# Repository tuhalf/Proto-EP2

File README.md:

# Proto - Educational Pupose 8-Bit Processor
Made for students, teachers, and any soul who wants to understand how a CPU works. Open Source.

Instruction Sets
 I : Instruction 
{ }: Register 
[ ]: Adress
( ): Condition - Based on registers A and B, takes parameters > or =
______________________________________________________________________
ADD [X]
	Add two numbers that are in A and B registers and write it to X address

SUB [X]- Subtract
	Subtract A from B and write it to X address 

LOAD {X} 
	Load data from next adress to X register 

STORE [X]
	Store data form register A to X adress in RAM 

LWJ {X} [Y] - Load With Jump
	Load data from Y adress to X register

JUMP [X]
	Jump to X adress in RAM

CJ (X) [Y] - Conditional Jump (Carry or Zero)
	If X condition is TRUE, jump to Y adress in RAM
  
LSCR [X] [Y]
	Loads the data stored in X address from RAM to Y address from GPU (Each bit is one pixel)
  
LSCR {X} [Y]
	Loads the data stored in X register to Y address from GPU (Each bit is one pixel)
  
LPNC [X]
	Starts loading the punch card starting from X address
  
HLT
	Halts the system

------------------------------------------------------------------------------------------------------------------------------------

Microcode Explained
bits
0nnnn00000nn00__
1000000000000000    HLT - 1
0100000000000000    REG_READ - 2
0010000000000000    AWRITE - 3	(Connected to ALUWRITE and Or'ed with AWRITE because there are not enough controll bits)
0001000000000000    FL - 4
0000100000000000    ALUWRITE - 5(Connected to RAM_WRITE and Or'ed with AWRITE because there are not enough controll bits)
0000010000000000    ALUSUB - 6
0000001000000000    PC_LE - 7
0000000100000000    PC_LRS - 8
0000000010000000    RAM_LRS - 9
0000000001000000    SLC_ADDR - 10
0000000000100000    RAM_OUT - 11
0000000000010000    INSTREAD - 12
0000000000001000    COUNT - 13
0000000000000100    RAM_AS - 14
0000000000000010    --
0000000000000001    --
01111000 00110000				00------000
----JUMP [X]---- (N-------,XXXXXXXX,XXXXXXXX)	nn100000                        
COUNT						00100000000 - 01111000 00111000
PC_LRS || RAM_OUT				00100000100 - 01111001 00010000
COUNT						00100000010 - 01111000 00111000	
RAM_OUT || PC_LE			        00100000110 - 01111010 00010000
RAM_OUT || INSTREAD				00100000001 - 01111000 00000000
----------------
----LOAD {X}---- (X-------)			                nn010000    
COUNT                                           00010000000 - 01111000 00111000
RAM_OUT || REG_READ                             00010000100 - 00111000 00010000
COUNT                                           00010000010 - 01111000 00111000
RAM_OUT || INSTREAD                             00010000110 - 01111000 00000000
----------------
----ADD [X]---- (N-------,XXXXXXXX,XXXXXXXX)    nn110000
COUNT || RAM_OUT || RAM_LRS || SLC_ADDR         00110000000 - 01111000 11011000
COUNT || RAM_OUT || SLC_ADDR                    00110000100 - 01111000 01011000
RAM_AS || ALUWRITE                              00110000010 - 01110000 00110100
RAM_OUT || INSTREAD                             00110000110 - 01111000 00000000
----------------
----SUB [X]---- (N-------,XXXXXXXX,XXXXXXXX)    nn001000
COUNT || RAM_OUT || RAM_LRS || SLC_ADDR         00001000000 - 01111000 11011000
COUNT || RAM_OUT || SLC_ADDR                    00001000100 - 01111000 01011000
RAM_AS || ALUSUB || ALUWRITE                    00001000010 - 01110100 00110100
RAM_OUT || INSTREAD                             00001000110 - 01111000 00000000
----------------
----STORE [X]---- (N-------,XXXXXXXX,XXXXXXXX)  nn101000
COUNT || RAM_OUT || RAM_LRS || SLC_ADDR         00101000000 - 01111000 11011000
COUNT || RAM_OUT || SLC_ADDR                    00101000100 - 01111000 01011000
RAM_AS || AWRITE                                00101000010 - 01011000 00110100
RAM_OUT || INSTREAD                             00101000110 - 01111000 00000000
-----------------
----LWJ {X} [Y]---- (X-------,YYYYYYYY,YYYYYYYY)nn111000
COUNT || RAM_OUT || RAM_LRS || SLC_ADDR         00111000000 - 01111000 11011000
COUNT || RAM_OUT || SLC_ADDR                    00111000100 - 01111000 01011000
RAM_AS || RAM_OUT || REG_READ                   00111000010 - 00111000 00010100
RAM_OUT || INSTREAD                             00111000110 - 01111000 00000000
-------------------
----CJ (ZERO) [Y]-- (N-1-----,XXXXXXXX,XXXXXXXX)nn001100
COUNT || FL                                     00001100000 - 01101000 00111000
01OOOOOO[PC_LRS || RAM_OUT                      01001100100 - 01111001 00010000
COUNT || RAM_OUT || PC_LE                       01001100010 - 01111010 00011000
RAM_OUT || INSTREAD]                            01001100110 - 01111000 00000000
COUNT                                           00001100100 - 01111000 00111000
COUNT || RAM_OUT || INSTREAD                    00001100010 - 01111000 00001000
---------------------
---CJ (CARRY) [Y]-- (N-1-----,XXXXXXXX,XXXXXXXX)nn100100
COUNT || FL                                     00100100000 - 01101000 00111000
10OOOOOO[PC_LRS || RAM_OUT                      10100100100 - 01111001 00010000
COUNT || RAM_OUT || PC_LE                       10100100010 - 01111010 00011000
RAM_OUT || INSTREAD]                            10100100110 - 01111000 00000000
COUNT                                           00100100100 - 01111000 00111000
COUNT || RAM_OUT || INSTREAD                    00100100010 - 01111000 00001000
---------------------
----HLT----                                     nn111111
HLT                                             00111111000 - 11111000 00110000
-----------

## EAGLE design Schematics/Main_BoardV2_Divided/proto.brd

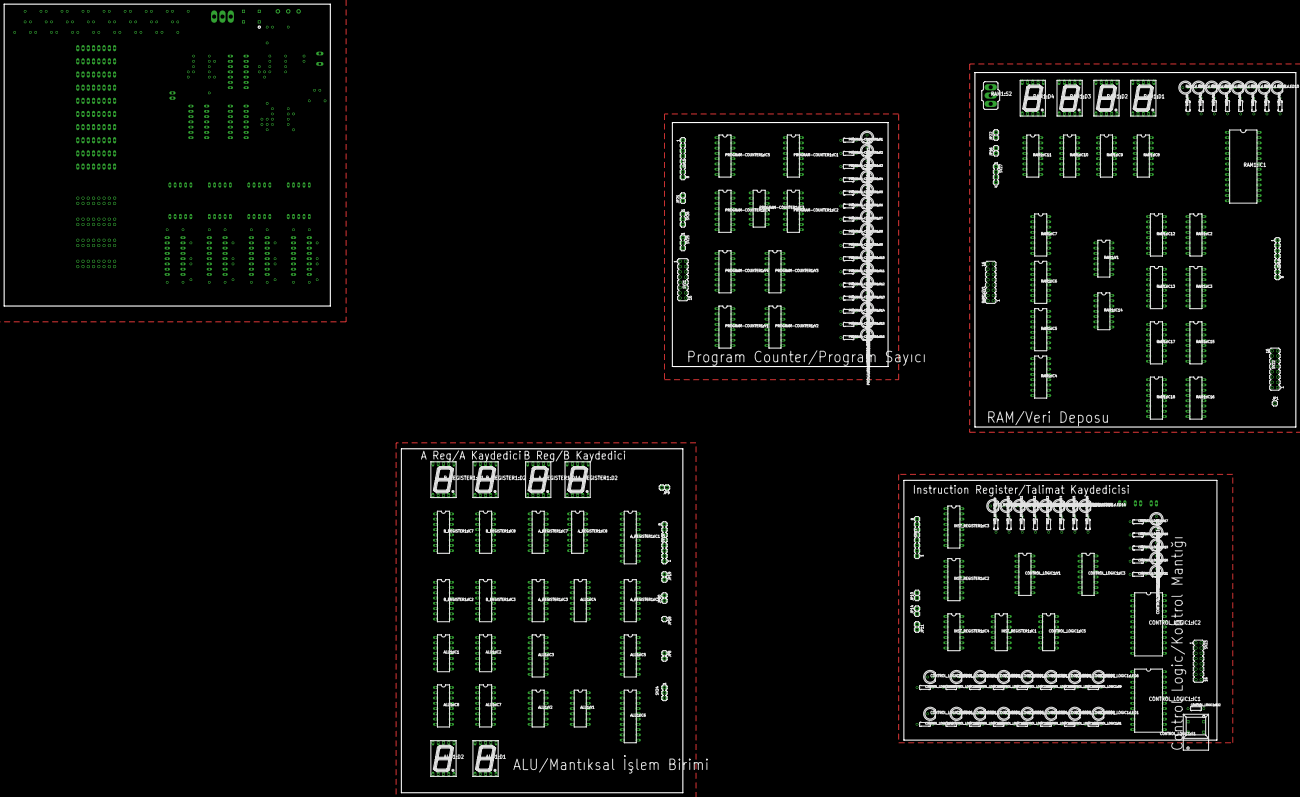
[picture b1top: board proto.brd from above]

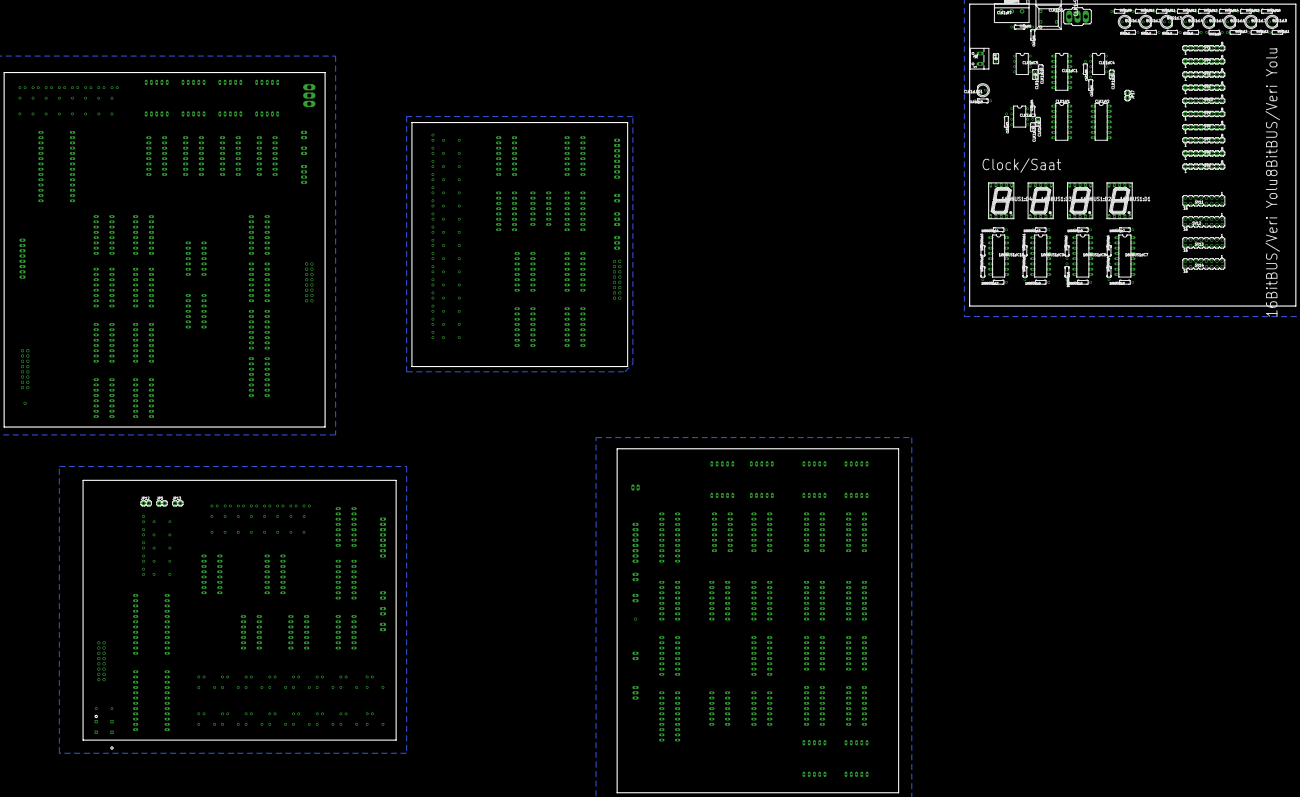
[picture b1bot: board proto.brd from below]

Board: 2 copper layers, 623.5 x 380.7 mm, 289 parts (90 on the bottom side), 422 nets, no tracks yet.

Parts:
16BBUS1:1, 16BBUS1:2, 16BBUS1:3, 16BBUS1:4, 16BBUS1:5, 16BBUS1:6, 16BBUS1:7, 16BBUS1:8, 16BBUS1:9, 16BBUS1:10, 16BBUS1:11, 16BBUS1:12, 16BBUS1:13, 16BBUS1:14, 16BBUS1:15, 16BBUS1:16: 10k; 0204/7
16BBUS1:D1, 16BBUS1:D2, 16BBUS1:D3, 16BBUS1:D4: 7SEG-13
16BBUS1:IC7, 16BBUS1:IC8, 16BBUS1:IC9, 16BBUS1:IC10: 74LS47N; DIL16
ALU1:D1, ALU1:D2: 7SEG-13
ALU1:IC1, ALU1:IC2: 74LS86N; DIL14
ALU1:IC3, ALU1:IC4: 74AC283N; DIL16
ALU1:IC5: 74HC173N; DIL16
ALU1:IC6: 74ACT245N; DIL20
ALU1:IC7, ALU1:IC8: 74LS47N; DIL16
ALU1:V1: 744002N; DIL14
ALU1:V2: 7409N; DIL14
A_REGISTER1:D1, A_REGISTER1:D2: 7SEG-13
A_REGISTER1:IC1: 74ACT245N; DIL20
A_REGISTER1:IC2, A_REGISTER1:IC3: 74HC173N; DIL16
A_REGISTER1:IC7, A_REGISTER1:IC8: 74LS47N; DIL16
BUS1:1, BUS1:2, BUS1:3, BUS1:5, BUS1:11, BUS1:12, BUS1:13, BUS1:15: 10k; 0204/7
BUS1:L1, BUS1:L2, BUS1:L3, BUS1:L4, BUS1:L5, BUS1:L6, BUS1:L7, BUS1:L8: LED5MM
BUS1:R9, BUS1:R10, BUS1:R11, BUS1:R12, BUS1:R13, BUS1:R14, BUS1:R15, BUS1:R16: 220; 0204/7
B_REGISTER1:D1, B_REGISTER1:D2: 7SEG-13
B_REGISTER1:IC2, B_REGISTER1:IC3: 74HC173N; DIL16
B_REGISTER1:IC7, B_REGISTER1:IC8: 74LS47N; DIL16
C1: 330uf; C025-025X050
CLK1:C1: 1uf; C025-024X044
CLK1:C2: 0.01uF; C025-025X050
CLK1:C3, CLK1:C5: 0.01uF; C025-024X044
CLK1:C4: 0.1uf; C025-024X044
CLK1:IC1: 74ALS09N; DIL14
CLK1:IC3, CLK1:IC4, CLK1:IC5: LM555N; DIL08
CLK1:LED1: LED5MM
CLK1:R1, CLK1:R2, CLK1:R3, CLK1:R4, CLK1:R5, CLK1:R6: 1k; 0204/7
CLK1:R7: 3RP/1610N
CLK1:R13: 220; 0204/7
CLK1:S1: 5501
CLK1:S2: 320-916
CLK1:V1: 7404N; DIL14
CLK1:V2: 7432N; DIL14
CONTROL_LOGIC1:IC1, CONTROL_LOGIC1:IC2: DIL24
CONTROL_LOGIC1:IC3: 74AC138N; DIL16
CONTROL_LOGIC1:IC5: 74AC00N; DIL14
CONTROL_LOGIC1:LED1, CONTROL_LOGIC1:LED2, CONTROL_LOGIC1:LED3, CONTROL_LOGIC1:LED4, CONTROL_LOGIC1:LED5, CONTROL_LOGIC1:LED6, CONTROL_LOGIC1:LED7, CONTROL_LOGIC1:LED8, CONTROL_LOGIC1:LED9, CONTROL_LOGIC1:LED10, CONTROL_LOGIC1:LED11, CONTROL_LOGIC1:LED12, CONTROL_LOGIC1:LED13, CONTROL_LOGIC1:LED14, CONTROL_LOGIC1:LED15, CONTROL_LOGIC1:LED16, CONTROL_LOGIC1:LED17, CONTROL_LOGIC1:LED18, CONTROL_LOGIC1:LED19, CONTROL_LOGIC1:LED20, CONTROL_LOGIC1:LED21: LED5MM
CONTROL_LOGIC1:R1, CONTROL_LOGIC1:R2, CONTROL_LOGIC1:R3, CONTROL_LOGIC1:R4, CONTROL_LOGIC1:R5, CONTROL_LOGIC1:R6, CONTROL_LOGIC1:R7, CONTROL_LOGIC1:R8, CONTROL_LOGIC1:R9, CONTROL_LOGIC1:R10, CONTROL_LOGIC1:R11, CONTROL_LOGIC1:R12, CONTROL_LOGIC1:R13, CONTROL_LOGIC1:R14, CONTROL_LOGIC1:R15, CONTROL_LOGIC1:R16, CONTROL_LOGIC1:R17, CONTROL_LOGIC1:R18, CONTROL_LOGIC1:R19, CONTROL_LOGIC1:R20, CONTROL_LOGIC1:R21, CONTROL_LOGIC1:R22: 220; 0204/7
CONTROL_LOGIC1:S1: 5501
CONTROL_LOGIC1:V1: 74161N; DIL16
INST_REGISTER1:IC1: 74ALS09N; DIL14
INST_REGISTER1:IC2, INST_REGISTER1:IC3: 74HC173N; DIL16
INST_REGISTER1:IC4: 74AC04N; DIL14
INST_REGISTER1:LED9, INST_REGISTER1:LED10, INST_REGISTER1:LED11, INST_REGISTER1:LED12, INST_REGISTER1:LED13, INST_REGISTER1:LED14, INST_REGISTER1:LED15, INST_REGISTER1:LED16: LED5MM
INST_REGISTER1:R9, INST_REGISTER1:R10, INST_REGISTER1:R11, INST_REGISTER1:R12, INST_REGISTER1:R13, INST_REGISTER1:R14, INST_REGISTER1:R15, INST_REGISTER1:R16: 220; 0204/7
JP1, JP18: 1X01
JP5, JP8, JP9, JP10, JP11, JP12, JP13, JP14, JP16, JP17, JP19, JP20, JP21, JP22: 1X02
PROGRAM-COUNTER1:IC1, PROGRAM-COUNTER1:IC2, PROGRAM-COUNTER1:IC4, PROGRAM-COUNTER1:IC5: 74HC173N; DIL16
PROGRAM-COUNTER1:IC3: 74AC04N; DIL14
PROGRAM-COUNTER1:LED1, PROGRAM-COUNTER1:LED2, PROGRAM-COUNTER1:LED3, PROGRAM-COUNTER1:LED4, PROGRAM-COUNTER1:LED5, PROGRAM-COUNTER1:LED6, PROGRAM-COUNTER1:LED7, PROGRAM-COUNTER1:LED8, PROGRAM-COUNTER1:LED9, PROGRAM-COUNTER1:LED10, PROGRAM-COUNTER1:LED11, PROGRAM-COUNTER1:LED12, PROGRAM-COUNTER1:LED13, PROGRAM-COUNTER1:LED14, PROGRAM-COUNTER1:LED15, PROGRAM-COUNTER1:LED16: LED5MM
PROGRAM-COUNTER1:R1, PROGRAM-COUNTER1:R2, PROGRAM-COUNTER1:R3, PROGRAM-COUNTER1:R4, PROGRAM-COUNTER1:R5, PROGRAM-COUNTER1:R6, PROGRAM-COUNTER1:R7, PROGRAM-COUNTER1:R8, PROGRAM-COUNTER1:R9, PROGRAM-COUNTER1:R10, PROGRAM-COUNTER1:R11, PROGRAM-COUNTER1:R12, PROGRAM-COUNTER1:R13, PROGRAM-COUNTER1:R14, PROGRAM-COUNTER1:R15, PROGRAM-COUNTER1:R16: 220; 0204/7
PROGRAM-COUNTER1:V1, PROGRAM-COUNTER1:V2, PROGRAM-COUNTER1:V3, PROGRAM-COUNTER1:V4: 74161N; DIL16
RAM1:D1, RAM1:D2, RAM1:D3, RAM1:D4: 7SEG-13
RAM1:IC1: CY62256LL-PC; DIL28-6
RAM1:IC2, RAM1:IC3, RAM1:IC12, RAM1:IC13: 74HC173N; DIL16
RAM1:IC4, RAM1:IC5, RAM1:IC6, RAM1:IC7, RAM1:IC15, RAM1:IC16, RAM1:IC17, RAM1:IC18: 74AC157N; DIL16
RAM1:IC8, RAM1:IC9, RAM1:IC10, RAM1:IC11: 74LS47N; DIL16
RAM1:IC14: 74AC04N; DIL14
RAM1:LED9, RAM1:LED10, RAM1:LED11, RAM1:LED12, RAM1:LED13, RAM1:LED14, RAM1:LED15, RAM1:LED16: LED5MM
RAM1:R9, RAM1:R10, RAM1:R11, RAM1:R12, RAM1:R13, RAM1:R14, RAM1:R15, RAM1:R16: 220; 0204/7
RAM1:S2: 320-916
RAM1:SV1: MA08-2
RAM1:V1: 7409N; DIL14
SV1, SV2, SV3, SV4, SV5, SV6, SV7, SV8, SV9, SV10, SV15, SV16, SV17, SV18: MA08-1
SV11, SV12, SV13, SV14, SV21, SV22, SV23: MA08-2
SV24, SV25, SV26: MA03-1
SV27: MA04-1
X1: W237-102

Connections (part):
8B_1: ALU1:IC6.18, A_REGISTER1:IC1.18, A_REGISTER1:IC3.14, B_REGISTER1:IC3.14, INST_REGISTER1:IC3.14, PROGRAM-COUNTER1:IC1.14, PROGRAM-COUNTER1:IC5.14, RAM1:IC1.11, RAM1:IC2.14, RAM1:IC12.14, RAM1:LED9.A, SV15.1, SV16.1, SV17.8, SV18.8
8B_2: ALU1:IC6.17, A_REGISTER1:IC1.17, A_REGISTER1:IC3.13, B_REGISTER1:IC3.13, INST_REGISTER1:IC3.13, PROGRAM-COUNTER1:IC1.13, PROGRAM-COUNTER1:IC5.13, RAM1:IC1.12, RAM1:IC2.13, RAM1:IC12.13, RAM1:LED10.A, SV15.2, SV16.2, SV17.7, SV18.7
8B_3: ALU1:IC6.16, A_REGISTER1:IC1.16, A_REGISTER1:IC3.12, B_REGISTER1:IC3.12, INST_REGISTER1:IC3.12, PROGRAM-COUNTER1:IC1.12, PROGRAM-COUNTER1:IC5.12, RAM1:IC1.13, RAM1:IC2.12, RAM1:IC12.12, RAM1:LED11.A, SV15.3, SV16.3, SV17.6, SV18.6
8B_4: ALU1:IC6.15, A_REGISTER1:IC1.15, A_REGISTER1:IC3.11, B_REGISTER1:IC3.11, INST_REGISTER1:IC3.11, PROGRAM-COUNTER1:IC1.11, PROGRAM-COUNTER1:IC5.11, RAM1:IC1.15, RAM1:IC2.11, RAM1:IC12.11, RAM1:LED12.A, SV15.4, SV16.4, SV17.5, SV18.5
8B_5: ALU1:IC6.14, A_REGISTER1:IC1.14, A_REGISTER1:IC2.14, INST_REGISTER1:IC2.14, PROGRAM-COUNTER1:IC2.14, PROGRAM-COUNTER1:IC4.14, RAM1:IC1.16, RAM1:IC3.14, RAM1:IC13.14, RAM1:LED13.A, SV15.5, SV16.5, SV17.4, SV18.4
8B_6: ALU1:IC6.13, A_REGISTER1:IC1.13, A_REGISTER1:IC2.13, INST_REGISTER1:IC2.13, PROGRAM-COUNTER1:IC2.13, PROGRAM-COUNTER1:IC4.13, RAM1:IC1.17, RAM1:IC3.13, RAM1:IC13.13, RAM1:LED14.A, SV15.6, SV16.6, SV17.3, SV18.3
8B_7: ALU1:IC6.12, A_REGISTER1:IC1.12, A_REGISTER1:IC2.12, INST_REGISTER1:IC2.12, PROGRAM-COUNTER1:IC2.12, PROGRAM-COUNTER1:IC4.12, RAM1:IC1.18, RAM1:IC3.12, RAM1:IC13.12, RAM1:LED15.A, SV15.7, SV16.7, SV17.2, SV18.2
8B_8: ALU1:IC6.11, A_REGISTER1:IC1.11, A_REGISTER1:IC2.11, INST_REGISTER1:IC2.11, PROGRAM-COUNTER1:IC2.11, PROGRAM-COUNTER1:IC4.11, RAM1:IC1.19, RAM1:IC3.11, RAM1:IC13.11, RAM1:LED16.A, SV15.8, SV16.8, SV17.1, SV18.1
16BBUS1:N$9: 16BBUS1:D1.7, 16BBUS1:IC7.13
16BBUS1:N$10: 16BBUS1:D1.6, 16BBUS1:IC7.12
16BBUS1:N$11: 16BBUS1:D1.4, 16BBUS1:IC7.11
16BBUS1:N$12: 16BBUS1:D1.2, 16BBUS1:IC7.10
16BBUS1:N$13: 16BBUS1:D1.1, 16BBUS1:IC7.9
16BBUS1:N$14: 16BBUS1:D1.9, 16BBUS1:IC7.15
16BBUS1:N$15: 16BBUS1:D1.10, 16BBUS1:IC7.14
16BBUS1:N$16: 16BBUS1:D2.7, 16BBUS1:IC8.13
16BBUS1:N$17: 16BBUS1:D4.7, 16BBUS1:IC10.13
16BBUS1:N$18: 16BBUS1:D4.6, 16BBUS1:IC10.12
16BBUS1:N$19: 16BBUS1:D4.4, 16BBUS1:IC10.11
16BBUS1:N$20: 16BBUS1:D4.2, 16BBUS1:IC10.10
16BBUS1:N$21: 16BBUS1:D2.6, 16BBUS1:IC8.12
16BBUS1:N$22: 16BBUS1:D2.4, 16BBUS1:IC8.11
16BBUS1:N$23: 16BBUS1:D2.2, 16BBUS1:IC8.10
16BBUS1:N$24: 16BBUS1:D2.1, 16BBUS1:IC8.9
16BBUS1:N$25: 16BBUS1:D4.1, 16BBUS1:IC10.9
16BBUS1:N$26: 16BBUS1:D4.9, 16BBUS1:IC10.15
16BBUS1:N$27: 16BBUS1:D4.10, 16BBUS1:IC10.14
16BBUS1:N$29: 16BBUS1:D2.9, 16BBUS1:IC8.15
16BBUS1:N$30: 16BBUS1:D2.10, 16BBUS1:IC8.14
16BBUS1:N$31: 16BBUS1:D3.7, 16BBUS1:IC9.13
16BBUS1:N$32: 16BBUS1:D3.6, 16BBUS1:IC9.12
16BBUS1:N$33: 16BBUS1:D3.4, 16BBUS1:IC9.11
16BBUS1:N$34: 16BBUS1:D3.2, 16BBUS1:IC9.10
16BBUS1:N$35: 16BBUS1:D3.1, 16BBUS1:IC9.9
16BBUS1:N$36: 16BBUS1:D3.9, 16BBUS1:IC9.15
16BBUS1:N$37: 16BBUS1:D3.10, 16BBUS1:IC9.14
16BBUS1:VCC: 16BBUS1:D1.3, 16BBUS1:D1.5, 16BBUS1:D1.8, 16BBUS1:D2.3, 16BBUS1:D2.5, 16BBUS1:D2.8, 16BBUS1:D3.3, 16BBUS1:D3.5, 16BBUS1:D3.8, 16BBUS1:D4.3, 16BBUS1:D4.5, 16BBUS1:D4.8, 16BBUS1:IC7.16, 16BBUS1:IC8.16, 16BBUS1:IC9.16, 16BBUS1:IC10.16
ALU1:+UB: ALU1:V1.14, ALU1:V2.14
ALU1:-UB: ALU1:V1.7, ALU1:V2.7
ALU1:A_9: ALU1:IC4.4, ALU1:IC6.9, ALU1:IC8.7, ALU1:V1.9
ALU1:A_10: ALU1:IC4.1, ALU1:IC6.8, ALU1:IC8.1, ALU1:V1.10
ALU1:A_11: ALU1:IC4.10, ALU1:IC6.6, ALU1:IC8.6, ALU1:V1.12
ALU1:A_12: ALU1:IC4.13, ALU1:IC6.7, ALU1:IC8.2, ALU1:V1.11
ALU1:A_13: ALU1:IC3.4, ALU1:IC6.5, ALU1:IC7.7, ALU1:V1.2
ALU1:A_14: ALU1:IC3.1, ALU1:IC6.4, ALU1:IC7.1, ALU1:V1.3
ALU1:A_15: ALU1:IC3.13, ALU1:IC6.3, ALU1:IC7.2, ALU1:V1.4
ALU1:A_16: ALU1:IC3.10, ALU1:IC6.2, ALU1:IC7.6, ALU1:V1.5
ALU1:N$1: ALU1:IC2.11, ALU1:IC4.6
ALU1:N$2: ALU1:IC2.8, ALU1:IC4.2
ALU1:N$3: ALU1:IC2.6, ALU1:IC4.15
ALU1:N$4: ALU1:IC2.3, ALU1:IC4.11
ALU1:N$5: ALU1:IC1.11, ALU1:IC3.6
ALU1:N$6: ALU1:IC1.6, ALU1:IC3.15
ALU1:N$7: ALU1:IC1.8, ALU1:IC3.2
ALU1:N$8: ALU1:IC1.3, ALU1:IC3.11
ALU1:N$9: ALU1:IC3.7, ALU1:IC4.9
ALU1:N$10: ALU1:D1.7, ALU1:IC7.13
ALU1:N$11: ALU1:D1.6, ALU1:IC7.12
ALU1:N$12: ALU1:D1.4, ALU1:IC7.11
ALU1:N$13: ALU1:D1.2, ALU1:IC7.10
ALU1:N$14: ALU1:D1.1, ALU1:IC7.9
ALU1:N$15: ALU1:D1.9, ALU1:IC7.15
ALU1:N$16: ALU1:D1.10, ALU1:IC7.14
ALU1:N$17: ALU1:D2.7, ALU1:IC8.13
ALU1:N$18: ALU1:V1.1, ALU1:V2.2
ALU1:N$19: ALU1:V1.13, ALU1:V2.1
ALU1:N$20: ALU1:IC5.14, ALU1:V2.3
ALU1:N$21: ALU1:D2.6, ALU1:IC8.12
ALU1:N$22: ALU1:D2.4, ALU1:IC8.11
ALU1:N$23: ALU1:D2.2, ALU1:IC8.10
ALU1:N$24: ALU1:D2.1, ALU1:IC8.9
ALU1:N$25: ALU1:IC3.9, ALU1:IC5.13
ALU1:N$29: ALU1:D2.9, ALU1:IC8.15
ALU1:N$30: ALU1:D2.10, ALU1:IC8.14
ALUSUB: CONTROL_LOGIC1:IC1.15, CONTROL_LOGIC1:LED3.A, SV23.11
A_REGISTER1:N$9: A_REGISTER1:D1.7, A_REGISTER1:IC7.13
A_REGISTER1:N$10: A_REGISTER1:D1.6, A_REGISTER1:IC7.12
A_REGISTER1:N$11: A_REGISTER1:D1.4, A_REGISTER1:IC7.11
A_REGISTER1:N$12: A_REGISTER1:D1.2, A_REGISTER1:IC7.10
A_REGISTER1:N$13: A_REGISTER1:D1.1, A_REGISTER1:IC7.9
A_REGISTER1:N$14: A_REGISTER1:D1.9, A_REGISTER1:IC7.15
A_REGISTER1:N$15: A_REGISTER1:D1.10, A_REGISTER1:IC7.14
A_REGISTER1:N$16: A_REGISTER1:D2.7, A_REGISTER1:IC8.13
A_REGISTER1:N$21: A_REGISTER1:D2.6, A_REGISTER1:IC8.12
A_REGISTER1:N$22: A_REGISTER1:D2.4, A_REGISTER1:IC8.11
A_REGISTER1:N$23: A_REGISTER1:D2.2, A_REGISTER1:IC8.10
A_REGISTER1:N$24: A_REGISTER1:D2.1, A_REGISTER1:IC8.9
A_REGISTER1:N$29: A_REGISTER1:D2.9, A_REGISTER1:IC8.15
A_REGISTER1:N$30: A_REGISTER1:D2.10, A_REGISTER1:IC8.14
BUS1:N$38: BUS1:L1.K, BUS1:R9.2
BUS1:N$39: BUS1:L2.K, BUS1:R10.2
BUS1:N$40: BUS1:L3.K, BUS1:R11.2
BUS1:N$41: BUS1:L4.K, BUS1:R12.2
BUS1:N$42: BUS1:L5.K, BUS1:R13.2
BUS1:N$43: BUS1:L6.K, BUS1:R14.2
BUS1:N$44: BUS1:L7.K, BUS1:R15.2
BUS1:N$45: BUS1:L8.K, BUS1:R16.2
B_REGISTER1:N$9: B_REGISTER1:D1.7, B_REGISTER1:IC7.13
B_REGISTER1:N$10: B_REGISTER1:D1.6, B_REGISTER1:IC7.12
B_REGISTER1:N$11: B_REGISTER1:D1.4, B_REGISTER1:IC7.11
B_REGISTER1:N$12: B_REGISTER1:D1.2, B_REGISTER1:IC7.10
B_REGISTER1:N$13: B_REGISTER1:D1.1, B_REGISTER1:IC7.9
B_REGISTER1:N$14: B_REGISTER1:D1.9, B_REGISTER1:IC7.15
B_REGISTER1:N$15: B_REGISTER1:D1.10, B_REGISTER1:IC7.14
B_REGISTER1:N$16: B_REGISTER1:D2.7, B_REGISTER1:IC8.13
B_REGISTER1:N$21: B_REGISTER1:D2.6, B_REGISTER1:IC8.12
B_REGISTER1:N$22: B_REGISTER1:D2.4, B_REGISTER1:IC8.11
B_REGISTER1:N$23: B_REGISTER1:D2.2, B_REGISTER1:IC8.10
B_REGISTER1:N$24: B_REGISTER1:D2.1, B_REGISTER1:IC8.9
B_REGISTER1:N$29: B_REGISTER1:D2.9, B_REGISTER1:IC8.15
B_REGISTER1:N$30: B_REGISTER1:D2.10, B_REGISTER1:IC8.14
B_REGISTER1:VCC: B_REGISTER1:IC2.16, B_REGISTER1:IC3.16, B_REGISTER1:IC7.16, B_REGISTER1:IC8.16
CF: ALU1:IC5.4, CONTROL_LOGIC1:IC1.7, CONTROL_LOGIC1:IC2.7, JP8.2, JP12.2
CLK: ALU1:IC5.7, A_REGISTER1:IC2.7, A_REGISTER1:IC3.7, B_REGISTER1:IC2.7, B_REGISTER1:IC3.7, CLK1:IC1.8, CLK1:LED1.A, CONTROL_LOGIC1:V1.2, INST_REGISTER1:IC2.7, INST_REGISTER1:IC3.7, JP14.1, JP16.1, JP17.1, JP20.1, PROGRAM-COUNTER1:IC1.7, PROGRAM-COUNTER1:IC2.7, PROGRAM-COUNTER1:IC4.7, PROGRAM-COUNTER1:IC5.7, PROGRAM-COUNTER1:V1.2, PROGRAM-COUNTER1:V2.2, PROGRAM-COUNTER1:V3.2, PROGRAM-COUNTER1:V4.2, RAM1:IC2.7, RAM1:IC3.7, RAM1:IC12.7, RAM1:IC13.7, SV25.3
CLK1:+UB: CLK1:V1.14, CLK1:V2.14
CLK1:-UB: CLK1:V1.7, CLK1:V2.7
CLK1:ACLK: CLK1:IC1.1, CLK1:IC5.3
CLK1:AMS: CLK1:IC1.2, CLK1:IC4.3, CLK1:V1.1
CLK1:MCLK: CLK1:IC1.5, CLK1:IC3.3
CLK1:N$1: CLK1:IC4.2, CLK1:R5.1, CLK1:S2.1
CLK1:N$2: CLK1:IC3.2, CLK1:R3.1, CLK1:S1.NO
CLK1:N$3: CLK1:IC4.4, CLK1:R6.1, CLK1:S2.3
CLK1:N$4: CLK1:C3.1, CLK1:IC3.5
CLK1:N$5: CLK1:C5.1, CLK1:IC4.5
CLK1:N$6: CLK1:LED1.K, CLK1:R13.2
CLK1:N$7: CLK1:C4.1, CLK1:IC3.6, CLK1:IC3.7, CLK1:R4.1
CLK1:N$8: CLK1:IC1.10, CLK1:V1.4
CLK1:N$9: CLK1:IC5.7, CLK1:R1.1, CLK1:R2.2
CLK1:N$10: CLK1:C2.1, CLK1:IC5.5
CLK1:N$11: CLK1:R2.1, CLK1:R7.2
CLK1:N$12: CLK1:IC1.6, CLK1:V2.2
CLK1:N$13: CLK1:IC1.3, CLK1:V2.1
CLK1:N$14: CLK1:IC1.9, CLK1:V2.3
CLK1:N$17: CLK1:IC1.4, CLK1:V1.2
CLK1:TRIGGER: CLK1:C1.1, CLK1:IC5.2, CLK1:IC5.6, CLK1:R7.3
CLR: ALU1:IC5.15, A_REGISTER1:IC2.15, A_REGISTER1:IC3.15, B_REGISTER1:IC2.15, B_REGISTER1:IC3.15, CONTROL_LOGIC1:IC5.8, INST_REGISTER1:IC2.15, INST_REGISTER1:IC3.15, JP13.1, JP14.2, JP16.2, JP20.2, PROGRAM-COUNTER1:IC1.15, PROGRAM-COUNTER1:IC2.15, PROGRAM-COUNTER1:IC4.15, PROGRAM-COUNTER1:IC5.15, RAM1:IC2.15, RAM1:IC3.15, RAM1:IC12.15, RAM1:IC13.15, SV25.2
CONTROL_LOGIC1:N$1: CONTROL_LOGIC1:IC1.19, CONTROL_LOGIC1:IC2.19, CONTROL_LOGIC1:IC3.1, CONTROL_LOGIC1:V1.12
CONTROL_LOGIC1:N$2: CONTROL_LOGIC1:IC1.22, CONTROL_LOGIC1:IC2.22, CONTROL_LOGIC1:IC3.2, CONTROL_LOGIC1:V1.13
CONTROL_LOGIC1:N$3: CONTROL_LOGIC1:IC1.23, CONTROL_LOGIC1:IC2.23, CONTROL_LOGIC1:IC3.3, CONTROL_LOGIC1:V1.14
CONTROL_LOGIC1:N$4: CONTROL_LOGIC1:IC3.10, CONTROL_LOGIC1:IC5.2
CONTROL_LOGIC1:N$5: CONTROL_LOGIC1:IC3.15, CONTROL_LOGIC1:LED9.A
CONTROL_LOGIC1:N$6: CONTROL_LOGIC1:IC3.14, CONTROL_LOGIC1:LED10.A
CONTROL_LOGIC1:N$7: CONTROL_LOGIC1:IC5.3, CONTROL_LOGIC1:IC5.12, CONTROL_LOGIC1:IC5.13
CONTROL_LOGIC1:N$8: CONTROL_LOGIC1:IC5.11, CONTROL_LOGIC1:V1.1
CONTROL_LOGIC1:N$9: CONTROL_LOGIC1:IC3.13, CONTROL_LOGIC1:LED11.A
CONTROL_LOGIC1:N$10: CONTROL_LOGIC1:IC3.12, CONTROL_LOGIC1:LED12.A
CONTROL_LOGIC1:N$11: CONTROL_LOGIC1:IC3.11, CONTROL_LOGIC1:LED13.A
CONTROL_LOGIC1:N$12: CONTROL_LOGIC1:LED6.K, CONTROL_LOGIC1:R9.2
CONTROL_LOGIC1:N$13: CONTROL_LOGIC1:LED7.K, CONTROL_LOGIC1:R10.2
CONTROL_LOGIC1:N$14: CONTROL_LOGIC1:LED8.K, CONTROL_LOGIC1:R11.2
CONTROL_LOGIC1:N$15: CONTROL_LOGIC1:LED17.K, CONTROL_LOGIC1:R12.2
CONTROL_LOGIC1:N$16: CONTROL_LOGIC1:LED18.K, CONTROL_LOGIC1:R13.2
CONTROL_LOGIC1:N$17: CONTROL_LOGIC1:LED19.K, CONTROL_LOGIC1:R14.2
CONTROL_LOGIC1:N$18: CONTROL_LOGIC1:LED20.K, CONTROL_LOGIC1:R15.2
CONTROL_LOGIC1:N$19: CONTROL_LOGIC1:LED21.K, CONTROL_LOGIC1:R16.2
CONTROL_LOGIC1:N$20: CONTROL_LOGIC1:LED1.K, CONTROL_LOGIC1:R1.2
CONTROL_LOGIC1:N$21: CONTROL_LOGIC1:LED2.K, CONTROL_LOGIC1:R2.2
CONTROL_LOGIC1:N$22: CONTROL_LOGIC1:LED3.K, CONTROL_LOGIC1:R3.2
CONTROL_LOGIC1:N$23: CONTROL_LOGIC1:LED4.K, CONTROL_LOGIC1:R4.2
CONTROL_LOGIC1:N$24: CONTROL_LOGIC1:LED5.K, CONTROL_LOGIC1:R5.2
CONTROL_LOGIC1:N$25: CONTROL_LOGIC1:LED14.K, CONTROL_LOGIC1:R6.2
CONTROL_LOGIC1:N$26: CONTROL_LOGIC1:LED15.K, CONTROL_LOGIC1:R7.2
CONTROL_LOGIC1:N$27: CONTROL_LOGIC1:IC5.4, CONTROL_LOGIC1:IC5.5, CONTROL_LOGIC1:R22.2, CONTROL_LOGIC1:S1.1B
CONTROL_LOGIC1:N$28: CONTROL_LOGIC1:LED16.K, CONTROL_LOGIC1:R8.2
CONTROL_LOGIC1:N$29: CONTROL_LOGIC1:LED9.K, CONTROL_LOGIC1:R17.2
CONTROL_LOGIC1:N$30: CONTROL_LOGIC1:LED10.K, CONTROL_LOGIC1:R18.2
CONTROL_LOGIC1:N$31: CONTROL_LOGIC1:LED11.K, CONTROL_LOGIC1:R19.2
CONTROL_LOGIC1:N$32: CONTROL_LOGIC1:LED12.K, CONTROL_LOGIC1:R20.2
CONTROL_LOGIC1:N$33: CONTROL_LOGIC1:LED13.K, CONTROL_LOGIC1:R21.2
COUNT: CONTROL_LOGIC1:IC2.14, CONTROL_LOGIC1:LED17.A, PROGRAM-COUNTER1:V1.7, PROGRAM-COUNTER1:V1.10, PROGRAM-COUNTER1:V2.7, PROGRAM-COUNTER1:V2.10, PROGRAM-COUNTER1:V3.7, PROGRAM-COUNTER1:V3.10, PROGRAM-COUNTER1:V4.7, PROGRAM-COUNTER1:V4.10, SV23.5, SV26.3
GND: 16BBUS1:1.1, 16BBUS1:2.1, 16BBUS1:3.1, 16BBUS1:4.1, 16BBUS1:5.1, 16BBUS1:6.1, 16BBUS1:7.1, 16BBUS1:8.1, 16BBUS1:9.1, 16BBUS1:10.1, 16BBUS1:11.1, 16BBUS1:12.1, 16BBUS1:13.1, 16BBUS1:14.1, 16BBUS1:15.1, 16BBUS1:16.1, 16BBUS1:IC7.3, 16BBUS1:IC7.4, 16BBUS1:IC7.5, 16BBUS1:IC8.3, 16BBUS1:IC8.4, 16BBUS1:IC8.5, 16BBUS1:IC9.3, 16BBUS1:IC9.4, 16BBUS1:IC9.5, 16BBUS1:IC10.3, 16BBUS1:IC10.4, 16BBUS1:IC10.5, ALU1:D1.3, ALU1:D1.5, ALU1:D1.8, ALU1:D2.3, ALU1:D2.5, ALU1:D2.8, ALU1:IC1.7, ALU1:IC2.7, ALU1:IC3.8, ALU1:IC4.8, ALU1:IC5.1, ALU1:IC5.2, ALU1:IC5.8, ALU1:IC6.10, ALU1:IC7.3, ALU1:IC7.4, ALU1:IC7.5, ALU1:IC7.8, ALU1:IC8.3, ALU1:IC8.4, ALU1:IC8.5, ALU1:IC8.8, A_REGISTER1:D1.3, A_REGISTER1:D1.5, A_REGISTER1:D1.8, A_REGISTER1:D2.3, A_REGISTER1:D2.5, A_REGISTER1:D2.8, A_REGISTER1:IC1.10, A_REGISTER1:IC2.1, A_REGISTER1:IC2.2, A_REGISTER1:IC2.8, A_REGISTER1:IC3.1, A_REGISTER1:IC3.2, A_REGISTER1:IC3.8, A_REGISTER1:IC7.3, A_REGISTER1:IC7.4, A_REGISTER1:IC7.5, A_REGISTER1:IC7.8, A_REGISTER1:IC8.3, A_REGISTER1:IC8.4, A_REGISTER1:IC8.5, A_REGISTER1:IC8.8, BUS1:1.1, BUS1:2.1, BUS1:3.1, BUS1:5.1, BUS1:11.2, BUS1:12.2, BUS1:13.2, BUS1:15.2, BUS1:R9.1, BUS1:R10.1, BUS1:R11.1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
HLT: CLK1:V1.3, CONTROL_LOGIC1:IC1.9, CONTROL_LOGIC1:LED16.A, JP17.2, SV23.16
INST_REGISTER1:INST_2: INST_REGISTER1:IC3.4, INST_REGISTER1:LED10.A
INST_REGISTER1:N$1: INST_REGISTER1:LED9.K, INST_REGISTER1:R9.2
INST_REGISTER1:N$2: INST_REGISTER1:LED10.K, INST_REGISTER1:R10.2
INST_REGISTER1:N$3: INST_REGISTER1:LED11.K, INST_REGISTER1:R11.2
INST_REGISTER1:N$4: INST_REGISTER1:IC1.1, INST_REGISTER1:IC4.2
INST_REGISTER1:N$5: INST_REGISTER1:LED12.K, INST_REGISTER1:R12.2
INST_REGISTER1:N$6: INST_REGISTER1:LED13.K, INST_REGISTER1:R13.2
INST_REGISTER1:N$7: INST_REGISTER1:LED14.K, INST_REGISTER1:R14.2
INST_REGISTER1:N$8: INST_REGISTER1:LED15.K, INST_REGISTER1:R15.2
INST_REGISTER1:N$9: INST_REGISTER1:LED16.K, INST_REGISTER1:R16.2
INST_REGISTER1:SLC_REG: INST_REGISTER1:IC1.4, INST_REGISTER1:IC3.3, INST_REGISTER1:IC4.1, INST_REGISTER1:LED9.A
INST_REGISTER1:VCC: INST_REGISTER1:IC1.14, INST_REGISTER1:IC2.16, INST_REGISTER1:IC3.16, INST_REGISTER1:IC4.14
unnamed: PROGRAM-COUNTER1:V4.14, SV21.1
unnamed: PROGRAM-COUNTER1:V4.13, SV21.2
unnamed: PROGRAM-COUNTER1:V4.12, SV21.3
unnamed: PROGRAM-COUNTER1:V4.11, SV21.4
unnamed: PROGRAM-COUNTER1:V3.14, SV21.5
unnamed: PROGRAM-COUNTER1:V3.13, SV21.6
unnamed: PROGRAM-COUNTER1:V3.12, SV21.7
unnamed: PROGRAM-COUNTER1:V3.11, SV21.8
unnamed: PROGRAM-COUNTER1:V1.14, SV21.9
unnamed: PROGRAM-COUNTER1:V1.13, SV21.10
unnamed: PROGRAM-COUNTER1:V1.12, SV21.11
unnamed: PROGRAM-COUNTER1:V1.11, SV21.12
unnamed: PROGRAM-COUNTER1:V2.14, SV21.13
unnamed: PROGRAM-COUNTER1:V2.13, SV21.14
unnamed: PROGRAM-COUNTER1:V2.12, SV21.15
unnamed: PROGRAM-COUNTER1:V2.11, SV21.16
unnamed: ALU1:IC4.5, A_REGISTER1:IC1.2, A_REGISTER1:IC3.3, A_REGISTER1:IC7.6
unnamed: ALU1:IC4.3, A_REGISTER1:IC1.3, A_REGISTER1:IC3.4, A_REGISTER1:IC7.2
unnamed: ALU1:IC4.14, A_REGISTER1:IC1.4, A_REGISTER1:IC3.5, A_REGISTER1:IC7.1
unnamed: ALU1:IC3.5, ALU1:IC4.12, A_REGISTER1:IC1.5, A_REGISTER1:IC1.6, A_REGISTER1:IC2.3, A_REGISTER1:IC3.6, A_REGISTER1:IC7.7, A_REGISTER1:IC8.6
unnamed: ALU1:IC3.3, A_REGISTER1:IC1.7, A_REGISTER1:IC2.4, A_REGISTER1:IC8.2
unnamed: ALU1:IC3.14, A_REGISTER1:IC1.8, A_REGISTER1:IC2.5, A_REGISTER1:IC8.1
unnamed: ALU1:IC3.12, A_REGISTER1:IC1.9, A_REGISTER1:IC2.6, A_REGISTER1:IC8.7
unnamed: ALU1:IC2.12, B_REGISTER1:IC3.3, B_REGISTER1:IC7.6
unnamed: ALU1:IC2.9, B_REGISTER1:IC3.4, B_REGISTER1:IC7.2
unnamed: ALU1:IC2.4, B_REGISTER1:IC3.5, B_REGISTER1:IC7.1
unnamed: ALU1:IC2.1, B_REGISTER1:IC3.6, B_REGISTER1:IC7.7
unnamed: ALU1:IC1.12, B_REGISTER1:IC2.3, B_REGISTER1:IC8.6
unnamed: ALU1:IC1.9, B_REGISTER1:IC2.4, B_REGISTER1:IC8.2
unnamed: ALU1:IC1.4, B_REGISTER1:IC2.5, B_REGISTER1:IC8.1
unnamed: ALU1:IC1.1, B_REGISTER1:IC2.6, B_REGISTER1:IC8.7
unnamed: CONTROL_LOGIC1:IC1.6, CONTROL_LOGIC1:IC2.6, INST_REGISTER1:IC3.5, INST_REGISTER1:LED11.A
unnamed: CONTROL_LOGIC1:IC1.5, CONTROL_LOGIC1:IC2.5, INST_REGISTER1:IC3.6, INST_REGISTER1:LED12.A
unnamed: CONTROL_LOGIC1:IC1.4, CONTROL_LOGIC1:IC2.4, INST_REGISTER1:IC2.3, INST_REGISTER1:LED13.A
unnamed: CONTROL_LOGIC1:IC1.3, CONTROL_LOGIC1:IC2.3, INST_REGISTER1:IC2.4, INST_REGISTER1:LED14.A
unnamed: CONTROL_LOGIC1:IC1.2, CONTROL_LOGIC1:IC2.2, INST_REGISTER1:IC2.5, INST_REGISTER1:LED15.A
unnamed: CONTROL_LOGIC1:IC1.1, CONTROL_LOGIC1:IC2.1, INST_REGISTER1:IC2.6, INST_REGISTER1:LED16.A
unnamed: BUS1:1.2, BUS1:L1.A, SV1.1, SV2.1, SV3.1, SV4.1, SV5.1, SV6.1, SV7.1, SV8.1, SV9.1, SV10.1
unnamed: BUS1:2.2, BUS1:L2.A, SV1.2, SV2.2, SV3.2, SV4.2, SV5.2, SV6.2, SV7.2, SV8.2, SV9.2, SV10.2
unnamed: BUS1:3.2, BUS1:L3.A, SV1.3, SV2.3, SV3.3, SV4.3, SV5.3, SV6.3, SV7.3, SV8.3, SV9.3, SV10.3
unnamed: BUS1:5.2, BUS1:L4.A, SV1.4, SV2.4, SV3.4, SV4.4, SV5.4, SV6.4, SV7.4, SV8.4, SV9.4, SV10.4
unnamed: BUS1:15.1, BUS1:L5.A, SV1.5, SV2.5, SV3.5, SV4.5, SV5.5, SV6.5, SV7.5, SV8.5, SV9.5, SV10.5
unnamed: BUS1:13.1, BUS1:L6.A, SV1.6, SV2.6, SV3.6, SV4.6, SV5.6, SV6.6, SV7.6, SV8.6, SV9.6, SV10.6
unnamed: BUS1:12.1, BUS1:L7.A, SV1.7, SV2.7, SV3.7, SV4.7, SV5.7, SV6.7, SV7.7, SV8.7, SV9.7, SV10.7
unnamed: BUS1:11.1, BUS1:L8.A, SV1.8, SV2.8, SV3.8, SV4.8, SV5.8, SV6.8, SV7.8, SV8.8, SV9.8, SV10.8
unnamed: 16BBUS1:4.2, 16BBUS1:IC7.6, SV11.1, SV12.1, SV13.1, SV14.1
unnamed: 16BBUS1:6.2, 16BBUS1:IC7.2, SV11.2, SV12.2, SV13.2, SV14.2
unnamed: 16BBUS1:7.2, 16BBUS1:IC7.1, SV11.3, SV12.3, SV13.3, SV14.3
unnamed: 16BBUS1:8.2, 16BBUS1:IC7.7, SV11.4, SV12.4, SV13.4, SV14.4
unnamed: 16BBUS1:1.2, 16BBUS1:IC8.6, SV11.5, SV12.5, SV13.5, SV14.5
unnamed: 16BBUS1:2.2, 16BBUS1:IC8.2, SV11.6, SV12.6, SV13.6, SV14.6
unnamed: 16BBUS1:3.2, 16BBUS1:IC8.1, SV11.7, SV12.7, SV13.7, SV14.7
unnamed: 16BBUS1:5.2, 16BBUS1:IC8.7, SV11.8, SV12.8, SV13.8, SV14.8
unnamed: 16BBUS1:12.2, 16BBUS1:IC9.6, SV11.9, SV12.9, SV13.9, SV14.9
unnamed: 16BBUS1:11.2, 16BBUS1:IC9.2, SV11.10, SV12.10, SV13.10, SV14.10
unnamed: 16BBUS1:10.2, 16BBUS1:IC9.1, SV11.11, SV12.11, SV13.11, SV14.11
unnamed: 16BBUS1:9.2, 16BBUS1:IC9.7, SV11.12, SV12.12, SV13.12, SV14.12
unnamed: 16BBUS1:16.2, 16BBUS1:IC10.6, SV11.13, SV12.13, SV13.13, SV14.13
unnamed: 16BBUS1:15.2, 16BBUS1:IC10.2, SV11.14, SV12.14, SV13.14, SV14.14
unnamed: 16BBUS1:14.2, 16BBUS1:IC10.1, SV11.15, SV12.15, SV13.15, SV14.15
unnamed: 16BBUS1:13.2, 16BBUS1:IC10.7, SV11.16, SV12.16, SV13.16, SV14.16
unnamed: RAM1:IC18.14, SV22.1
unnamed: RAM1:IC18.11, SV22.2
unnamed: RAM1:IC18.5, SV22.3
unnamed: RAM1:IC18.2, SV22.4
unnamed: RAM1:IC15.5, SV22.15
unnamed: RAM1:IC15.2, SV22.16
unnamed: RAM1:IC15.14, SV22.13
unnamed: RAM1:IC15.11, SV22.14
unnamed: RAM1:IC16.5, SV22.11
unnamed: RAM1:IC16.2, SV22.12
unnamed: RAM1:IC16.11, SV22.10
unnamed: RAM1:IC16.14, SV22.9
unnamed: RAM1:IC17.2, SV22.8
unnamed: RAM1:IC17.5, SV22.7
unnamed: RAM1:IC17.11, SV22.6
unnamed: RAM1:IC17.14, SV22.5
unnamed: 16BBUS1:IC7.8, 16BBUS1:IC8.8, 16BBUS1:IC9.8, 16BBUS1:IC10.8
unnamed: CONTROL_LOGIC1:IC2.15, CONTROL_LOGIC1:LED8.A, SV23.3
unnamed: CONTROL_LOGIC1:IC2.16, CONTROL_LOGIC1:LED7.A, SV23.2
unnamed: CONTROL_LOGIC1:IC2.17, CONTROL_LOGIC1:LED6.A, SV23.1
NNOW2: JP1.1, RAM1:IC15.1, RAM1:IC16.1, RAM1:IC17.1, RAM1:IC18.1
PC_LE: CONTROL_LOGIC1:IC1.16, CONTROL_LOGIC1:LED2.A, PROGRAM-COUNTER1:V1.9, PROGRAM-COUNTER1:V2.9, PROGRAM-COUNTER1:V3.9, PROGRAM-COUNTER1:V4.9, SV23.10, SV26.2
PC_LRS: CONTROL_LOGIC1:IC1.17, CONTROL_LOGIC1:LED1.A, PROGRAM-COUNTER1:IC1.9, PROGRAM-COUNTER1:IC1.10, PROGRAM-COUNTER1:IC2.9, PROGRAM-COUNTER1:IC2.10, PROGRAM-COUNTER1:IC3.1, SV23.9, SV26.1
PROGRAM-COUNTER1:+UB: PROGRAM-COUNTER1:V1.16, PROGRAM-COUNTER1:V2.16, PROGRAM-COUNTER1:V3.16, PROGRAM-COUNTER1:V4.16
PROGRAM-COUNTER1:-UB: PROGRAM-COUNTER1:V1.8, PROGRAM-COUNTER1:V2.8, PROGRAM-COUNTER1:V3.8, PROGRAM-COUNTER1:V4.8
PROGRAM-COUNTER1:N$1: PROGRAM-COUNTER1:IC1.6, PROGRAM-COUNTER1:LED13.A, PROGRAM-COUNTER1:V1.6
PROGRAM-COUNTER1:N$2: PROGRAM-COUNTER1:IC2.6, PROGRAM-COUNTER1:LED9.A, PROGRAM-COUNTER1:V2.6
PROGRAM-COUNTER1:N$3: PROGRAM-COUNTER1:IC2.5, PROGRAM-COUNTER1:LED10.A, PROGRAM-COUNTER1:V2.5
PROGRAM-COUNTER1:N$4: PROGRAM-COUNTER1:IC2.4, PROGRAM-COUNTER1:LED11.A, PROGRAM-COUNTER1:V2.4
PROGRAM-COUNTER1:N$5: PROGRAM-COUNTER1:IC2.3, PROGRAM-COUNTER1:LED12.A, PROGRAM-COUNTER1:V2.3
PROGRAM-COUNTER1:N$6: PROGRAM-COUNTER1:IC1.5, PROGRAM-COUNTER1:LED14.A, PROGRAM-COUNTER1:V1.5
PROGRAM-COUNTER1:N$7: PROGRAM-COUNTER1:IC1.4, PROGRAM-COUNTER1:LED15.A, PROGRAM-COUNTER1:V1.4
PROGRAM-COUNTER1:N$8: PROGRAM-COUNTER1:IC1.3, PROGRAM-COUNTER1:LED16.A, PROGRAM-COUNTER1:V1.3
PROGRAM-COUNTER1:N$17: PROGRAM-COUNTER1:IC4.6, PROGRAM-COUNTER1:LED1.A, PROGRAM-COUNTER1:V3.6
PROGRAM-COUNTER1:N$18: PROGRAM-COUNTER1:IC4.5, PROGRAM-COUNTER1:LED2.A, PROGRAM-COUNTER1:V3.5
PROGRAM-COUNTER1:N$19: PROGRAM-COUNTER1:IC4.4, PROGRAM-COUNTER1:LED3.A, PROGRAM-COUNTER1:V3.4
PROGRAM-COUNTER1:N$20: PROGRAM-COUNTER1:IC4.3, PROGRAM-COUNTER1:LED4.A, PROGRAM-COUNTER1:V3.3
PROGRAM-COUNTER1:N$25: PROGRAM-COUNTER1:IC5.6, PROGRAM-COUNTER1:LED5.A, PROGRAM-COUNTER1:V4.6
PROGRAM-COUNTER1:N$26: PROGRAM-COUNTER1:IC5.5, PROGRAM-COUNTER1:LED6.A, PROGRAM-COUNTER1:V4.5
PROGRAM-COUNTER1:N$27: PROGRAM-COUNTER1:IC5.4, PROGRAM-COUNTER1:LED7.A, PROGRAM-COUNTER1:V4.4
PROGRAM-COUNTER1:N$28: PROGRAM-COUNTER1:IC5.3, PROGRAM-COUNTER1:LED8.A, PROGRAM-COUNTER1:V4.3
PROGRAM-COUNTER1:N$45: PROGRAM-COUNTER1:LED9.K, PROGRAM-COUNTER1:R9.2
PROGRAM-COUNTER1:N$46: PROGRAM-COUNTER1:LED10.K, PROGRAM-COUNTER1:R10.2
PROGRAM-COUNTER1:N$47: PROGRAM-COUNTER1:LED11.K, PROGRAM-COUNTER1:R11.2
PROGRAM-COUNTER1:N$48: PROGRAM-COUNTER1:LED12.K, PROGRAM-COUNTER1:R12.2
PROGRAM-COUNTER1:N$49: PROGRAM-COUNTER1:LED13.K, PROGRAM-COUNTER1:R13.2
PROGRAM-COUNTER1:N$50: PROGRAM-COUNTER1:LED14.K, PROGRAM-COUNTER1:R14.2
PROGRAM-COUNTER1:N$51: PROGRAM-COUNTER1:LED15.K, PROGRAM-COUNTER1:R15.2
PROGRAM-COUNTER1:N$52: PROGRAM-COUNTER1:LED16.K, PROGRAM-COUNTER1:R16.2
PROGRAM-COUNTER1:N$53: PROGRAM-COUNTER1:LED1.K, PROGRAM-COUNTER1:R1.2
PROGRAM-COUNTER1:N$54: PROGRAM-COUNTER1:LED2.K, PROGRAM-COUNTER1:R2.2
PROGRAM-COUNTER1:N$55: PROGRAM-COUNTER1:LED3.K, PROGRAM-COUNTER1:R3.2
PROGRAM-COUNTER1:N$56: PROGRAM-COUNTER1:LED4.K, PROGRAM-COUNTER1:R4.2
PROGRAM-COUNTER1:N$57: PROGRAM-COUNTER1:LED5.K, PROGRAM-COUNTER1:R5.2
PROGRAM-COUNTER1:N$58: PROGRAM-COUNTER1:LED6.K, PROGRAM-COUNTER1:R6.2
PROGRAM-COUNTER1:N$59: PROGRAM-COUNTER1:LED7.K, PROGRAM-COUNTER1:R7.2
PROGRAM-COUNTER1:N$60: PROGRAM-COUNTER1:LED8.K, PROGRAM-COUNTER1:R8.2
PROGRAM-COUNTER1:VCC: PROGRAM-COUNTER1:IC1.16, PROGRAM-COUNTER1:IC2.16, PROGRAM-COUNTER1:IC3.14, PROGRAM-COUNTER1:IC4.16, PROGRAM-COUNTER1:IC5.16
PROGRAM-COUNTER1:|LRS: PROGRAM-COUNTER1:IC3.2, PROGRAM-COUNTER1:IC4.9, PROGRAM-COUNTER1:IC4.10, PROGRAM-COUNTER1:IC5.9, PROGRAM-COUNTER1:IC5.10
RAM1:A/M: RAM1:IC4.1, RAM1:IC5.1, RAM1:IC6.1, RAM1:IC7.1, RAM1:S2.2
RAM1:N$1: RAM1:IC12.9, RAM1:IC12.10, RAM1:IC13.9, RAM1:IC13.10, RAM1:V1.6
RAM1:N$2: RAM1:IC2.9, RAM1:IC2.10, RAM1:IC3.9, RAM1:IC3.10, RAM1:V1.3
RAM1:N$3: RAM1:IC14.2, RAM1:V1.5
RAM1:N$4: RAM1:IC4.2, RAM1:IC15.4
RAM1:N$5: RAM1:IC4.5, RAM1:IC15.7
RAM1:N$6: RAM1:IC4.11, RAM1:IC15.9
RAM1:N$7: RAM1:IC4.14, RAM1:IC15.12
RAM1:N$8: RAM1:IC5.2, RAM1:IC16.4
RAM1:N$9: RAM1:IC5.5, RAM1:IC16.7
RAM1:N$10: RAM1:IC5.11, RAM1:IC16.9
RAM1:N$11: RAM1:IC5.14, RAM1:IC16.12
RAM1:N$12: RAM1:IC6.2, RAM1:IC17.4
RAM1:N$13: RAM1:IC6.5, RAM1:IC17.7
RAM1:N$14: RAM1:IC6.11, RAM1:IC17.9
RAM1:N$15: RAM1:IC6.14, RAM1:IC17.12
RAM1:N$16: RAM1:IC7.2, RAM1:IC18.4
RAM1:N$17: RAM1:IC7.5, RAM1:IC18.7
RAM1:N$18: RAM1:IC7.11, RAM1:IC18.9
RAM1:N$19: RAM1:IC7.14, RAM1:IC18.12
RAM1:N$20: RAM1:IC4.3, RAM1:SV1.1
RAM1:N$21: RAM1:IC4.6, RAM1:SV1.2
RAM1:N$22: RAM1:IC4.10, RAM1:SV1.3
RAM1:N$23: RAM1:IC4.13, RAM1:SV1.4
RAM1:N$24: RAM1:IC5.3, RAM1:SV1.5
RAM1:N$25: RAM1:IC5.6, RAM1:SV1.6
RAM1:N$26: RAM1:IC5.10, RAM1:SV1.7
RAM1:N$27: RAM1:IC5.13, RAM1:SV1.8
RAM1:N$28: RAM1:IC6.3, RAM1:SV1.9
RAM1:N$29: RAM1:IC6.6, RAM1:SV1.10
RAM1:N$30: RAM1:IC6.10, RAM1:SV1.11
RAM1:N$31: RAM1:IC6.13, RAM1:SV1.12
RAM1:N$32: RAM1:IC7.3, RAM1:SV1.13
RAM1:N$33: RAM1:IC7.10, RAM1:SV1.15
RAM1:N$34: RAM1:IC7.13, RAM1:SV1.16
RAM1:N$35: RAM1:IC7.6, RAM1:SV1.14
RAM1:N$36: RAM1:IC1.21, RAM1:IC4.4, RAM1:IC11.7
RAM1:N$37: RAM1:IC1.23, RAM1:IC4.7, RAM1:IC11.1
RAM1:N$38: RAM1:D1.7, RAM1:IC8.13
RAM1:N$39: RAM1:D1.6, RAM1:IC8.12
RAM1:N$40: RAM1:IC1.24, RAM1:IC4.9, RAM1:IC11.2
RAM1:N$41: RAM1:IC1.25, RAM1:IC4.12, RAM1:IC11.6
RAM1:N$42: RAM1:IC1.26, RAM1:IC5.4, RAM1:IC10.7
RAM1:N$43: RAM1:IC1.1, RAM1:IC5.7, RAM1:IC10.1
RAM1:N$44: RAM1:IC1.2, RAM1:IC5.9, RAM1:IC10.2
RAM1:N$45: RAM1:IC1.3, RAM1:IC5.12, RAM1:IC10.6
RAM1:N$46: RAM1:IC1.4, RAM1:IC6.4, RAM1:IC9.7
RAM1:N$47: RAM1:IC1.5, RAM1:IC6.7, RAM1:IC9.1
RAM1:N$48: RAM1:IC1.6, RAM1:IC6.9, RAM1:IC9.2
RAM1:N$49: RAM1:IC1.7, RAM1:IC6.12, RAM1:IC9.6
RAM1:N$50: RAM1:IC1.8, RAM1:IC7.4, RAM1:IC8.7
RAM1:N$51: RAM1:IC1.9, RAM1:IC7.7, RAM1:IC8.1
RAM1:N$52: RAM1:IC1.10, RAM1:IC7.9, RAM1:IC8.2
RAM1:N$53: RAM1:IC2.3, RAM1:IC15.3
RAM1:N$54: RAM1:D1.4, RAM1:IC8.11
RAM1:N$55: RAM1:D1.2, RAM1:IC8.10
RAM1:N$56: RAM1:D1.1, RAM1:IC8.9
RAM1:N$57: RAM1:D1.9, RAM1:IC8.15
RAM1:N$58: RAM1:D1.10, RAM1:IC8.14
RAM1:N$59: RAM1:D2.7, RAM1:IC9.13
RAM1:N$60: RAM1:D2.6, RAM1:IC9.12
RAM1:N$61: RAM1:D2.4, RAM1:IC9.11
RAM1:N$62: RAM1:D2.2, RAM1:IC9.10
RAM1:N$63: RAM1:D2.1, RAM1:IC9.9
RAM1:N$64: RAM1:D2.9, RAM1:IC9.15
RAM1:N$65: RAM1:D2.10, RAM1:IC9.14
RAM1:N$66: RAM1:D3.7, RAM1:IC10.13
RAM1:N$67: RAM1:D3.6, RAM1:IC10.12
RAM1:N$68: RAM1:D3.4, RAM1:IC10.11
RAM1:N$69: RAM1:D3.2, RAM1:IC10.10
RAM1:N$70: RAM1:D3.1, RAM1:IC10.9
RAM1:N$71: RAM1:D3.9, RAM1:IC10.15
RAM1:N$72: RAM1:D3.10, RAM1:IC10.14
RAM1:N$73: RAM1:D4.7, RAM1:IC11.13
RAM1:N$74: RAM1:D4.6, RAM1:IC11.12
RAM1:N$75: RAM1:D4.4, RAM1:IC11.11
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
